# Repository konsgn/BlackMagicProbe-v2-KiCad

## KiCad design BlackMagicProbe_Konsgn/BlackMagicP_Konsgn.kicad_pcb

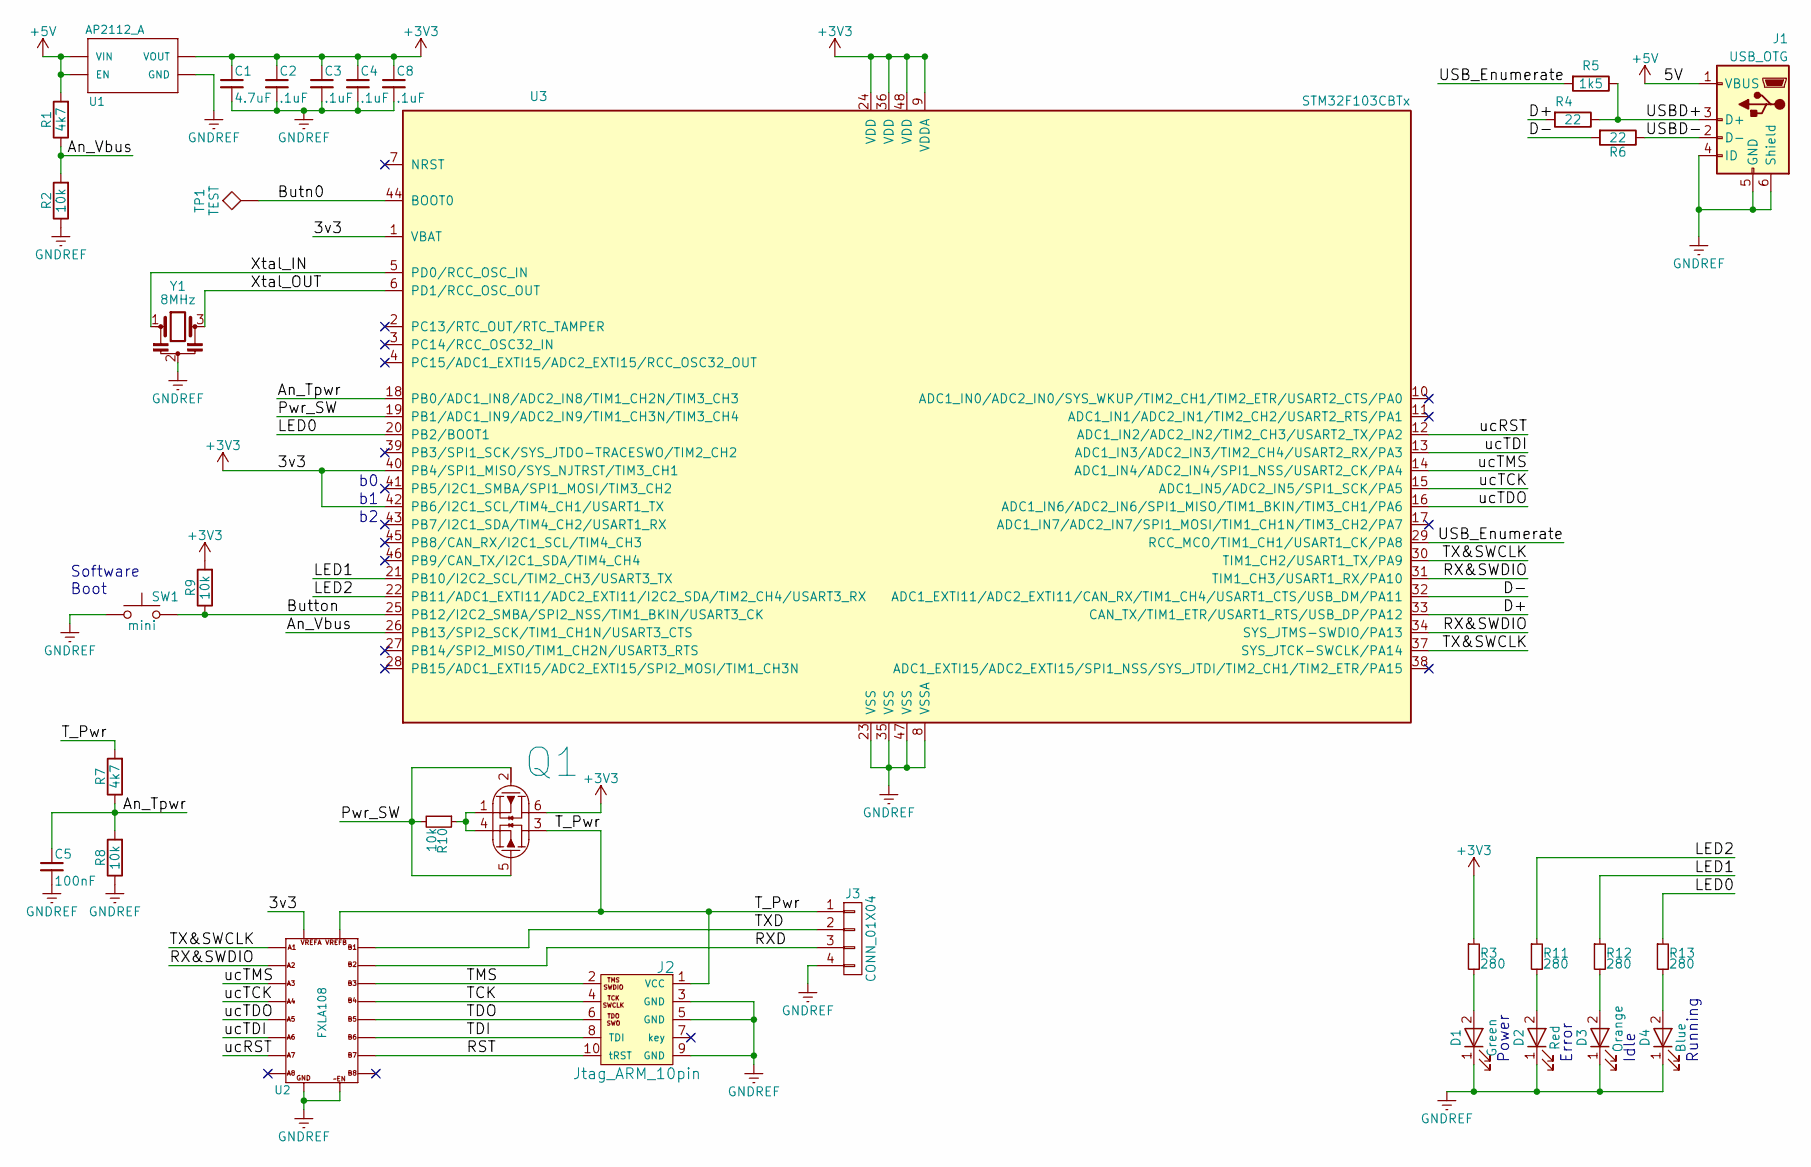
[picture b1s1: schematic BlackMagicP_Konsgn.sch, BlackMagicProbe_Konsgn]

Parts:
C1: 4.7uF; C_0603
C2, C3, C4, C8: .1uF; C_0603
C5: 100nF; C_0603
D1: Green; LED_0603
D2: Red; LED_0603
D3: Orange; LED_0603
D4: Blue; LED_0603
J1: USB_OTG; Homebrew-USB-B-MICRO-SMD_PINS
J2: Jtag_ARM_10pin; CNX_2X05X1.27_Vertical_SMD
J3: CONN_01X04; Pin_Header_Angled_1x04_Pitch2.54mm_SMD_Pin1Right
Q1: Q2-PMOS-S2G2D1S1G1D2; SOT563-6
R1, R7: 4k7; R_0603
R2, R8, R9, R10: 10k; R_0603
R3, R11, R12, R13: 280; R_0603
R4, R6: 22; R_0603
R5: 1k5; R_0603
SW1: mini; Homebrew-SMT_SPSD_5X3MM
TP1: TEST; Measurement_Point_Round-SMD-Pad_Small
U1: AP2112_A; Homebrew-SOT23-5
U2: FXLA108; Homebrew-DHVQFN20
U3: STM32F103CBTx; LQFP-48_7x7mm_Pitch0.5mm
Y1: 8MHz; Resonator_SMD_muRata_SFSKA-3pin_7.9x3.8mm_HandSoldering

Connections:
+3V3: C1.1, C2.1, C3.1, C4.1, C8.1, Q1.6, R3.1, R9.2, U1.5 (VOUT), U2.1, U3.1 (VBAT), U3.9 (VDDA), U3.24 (VDD), U3.36 (VDD), U3.40 (PB4/SPI1_MISO/SYS_NJTRST/TIM3_CH1), U3.42 (PB6/I2C1_SCL/TIM4_CH1/USART1_TX), U3.48 (VDD)
+5V: J1.1 (VBUS), R1.2, U1.1 (VIN), U1.3 (EN)
/An_Tpwr: C5.1, R7.1, R8.2, U3.18 (PB0/ADC1_IN8/ADC2_IN8/TIM1_CH2N/TIM3_CH3)
/An_Vbus: R1.1, R2.2, U3.26 (PB13/SPI2_SCK/TIM1_CH1N/USART3_CTS)
/Butn0: TP1.1, U3.44 (BOOT0)
/Button: R9.1, SW1.2, U3.25 (PB12/I2C2_SMBA/SPI2_NSS/TIM1_BKIN/USART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)
/D+: R4.2, U3.33 (CAN_TX/TIM1_ETR/USART1_RTS/USB_DP/PA12)
/D-: R6.2, U3.32 (ADC1_EXTI11/ADC2_EXTI11/CAN_RX/TIM1_CH4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)
/LED0: R13.1, U3.20 (PB2/BOOT1)
/LED1: R12.1, U3.21 (PB10/I2C2_SCL/TIM2_CH3/USART3_TX)
/LED2: R11.1, U3.22 (PB11/ADC1_EXTI11/ADC2_EXTI11/I2C2_SDA/T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)
/Pwr_SW: Q1.2, Q1.5, R10.2, U3.19 (PB1/ADC1_IN9/ADC2_IN9/TIM1_CH3N/TIM3_CH4)
/RST: J2.10 (tRST), U2.13
/RX&SWDIO: U2.3, U3.31 (TIM1_CH3/USART1_RX/PA10), U3.34 (SYS_JTMS-SWDIO/PA13)
/RXD: J3.3, U2.18
/TCK: J2.4, U2.16
/TDI: J2.8 (TDI), U2.14
/TDO: J2.6, U2.15
/TMS: J2.2, U2.17
/TX&SWCLK: U2.2, U3.30 (TIM1_CH2/USART1_TX/PA9), U3.37 (SYS_JTCK-SWCLK/PA14)
/TXD: J3.2, U2.19
/T_Pwr: J2.1 (VCC), J3.1, Q1.3, R7.2, U2.20
/USBD+: J1.3 (D+), R4.1, R5.1
/USBD-: J1.2 (D-), R6.1
/USB_Enumerate: R5.2, U3.29 (RCC_MCO/TIM1_CH1/USART1_CK/PA8)
/Xtal_IN: U3.5 (PD0/RCC_OSC_IN), Y1.1
/Xtal_OUT: U3.6 (PD1/RCC_OSC_OUT), Y1.3
/ucRST: U2.8, U3.12 (ADC1_IN2/ADC2_IN2/TIM2_CH3/USART2_TX/PA2)
/ucTCK: U2.5, U3.15 (ADC1_IN5/ADC2_IN5/SPI1_SCK/PA5)
/ucTDI: U2.7, U3.13 (ADC1_IN3/ADC2_IN3/TIM2_CH4/USART2_RX/PA3)
/ucTDO: U2.6, U3.16 (ADC1_IN6/ADC2_IN6/SPI1_MISO/TIM1_BKIN/T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)
/ucTMS: U2.4, U3.14 (ADC1_IN4/ADC2_IN4/SPI1_NSS/USART2_CK/PA4)
GNDREF: C1.2, C2.2, C3.2, C4.2, C5.2, C8.2, D1.1 (K), D2.1 (K), D3.1 (K), D4.1 (K), J1.4 (ID), J1.5 (GND), J1.6 (Shield), J2.3 (GND), J2.5 (GND), J2.9 (GND), J3.4, R2.1, R8.1, SW1.1, U1.2 (GND), U2.10, U2.11, U3.8 (VSSA), U3.23 (VSS), U3.35 (VSS), U3.47 (VSS), Y1.2
unnamed: D1.2 (A), R3.2
unnamed: D2.2 (A), R11.2
unnamed: D3.2 (A), R12.2
unnamed: D4.2 (A), R13.2
unnamed: Q1.1, Q1.4, R10.1

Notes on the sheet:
Running
Idle
Error
Power
Software Boot

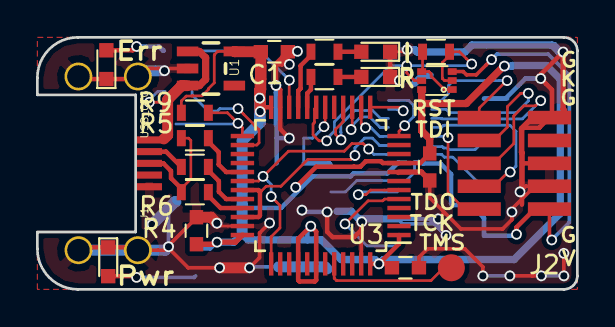
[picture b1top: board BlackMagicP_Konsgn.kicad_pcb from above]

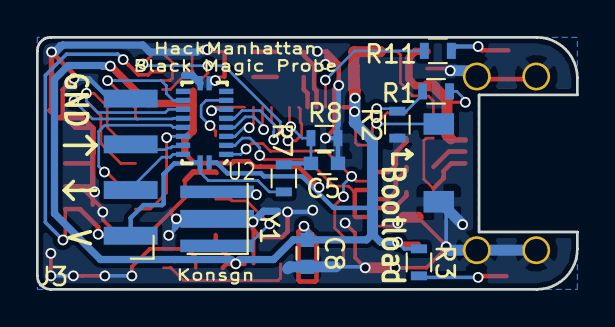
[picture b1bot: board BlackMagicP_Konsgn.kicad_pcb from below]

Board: 2 copper layers, 30.0 x 14.0 mm, 33 parts (12 on the bottom side), 38 nets.

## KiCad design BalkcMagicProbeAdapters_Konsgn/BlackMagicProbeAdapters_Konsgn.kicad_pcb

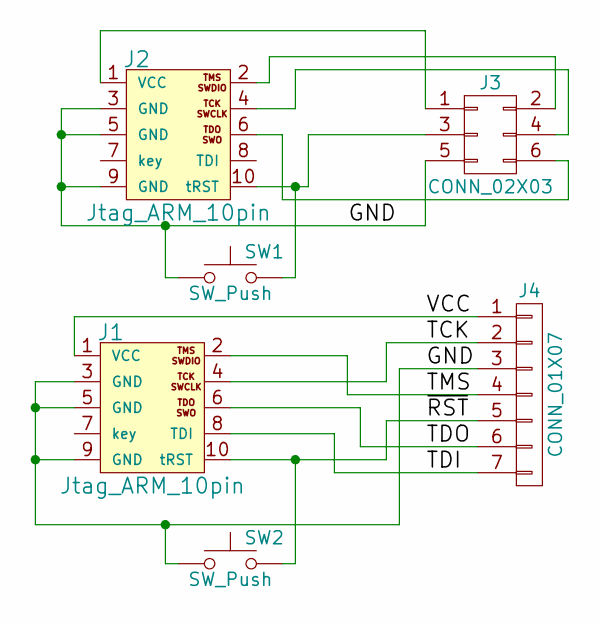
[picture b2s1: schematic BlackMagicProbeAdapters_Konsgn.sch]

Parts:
J1, J2: Jtag_ARM_10pin; CNX_2X05X1.27_Vertical_SMD
J3: CONN_02X03; Pin_Header_Straight_2x03_Pitch2.54mm_SMD
J4: CONN_01X07; Pin_Header_Angled_1x07_Pitch2.54mm
SW1, SW2: SW_Push; Homebrew-SMT_SPSD_5X3MM

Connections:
/GND: J1.3 (GND), J1.5 (GND), J1.9 (GND), J2.3 (GND), J2.5 (GND), J2.9 (GND), J3.5, J4.3, SW1.1, SW2.1
/TCK: J1.4, J4.2
/TDI: J1.8 (TDI), J4.7
/TDO: J1.6, J4.6
/TMS: J1.2, J4.4
/VCC: J1.1 (VCC), J4.1
/~RST: J1.10 (tRST), J4.5, SW2.2
unnamed: J2.1 (VCC), J3.1
unnamed: J2.2, J3.2
unnamed: J2.4, J3.4
unnamed: J2.6, J3.6
unnamed: J2.10 (tRST), J3.3, SW1.2

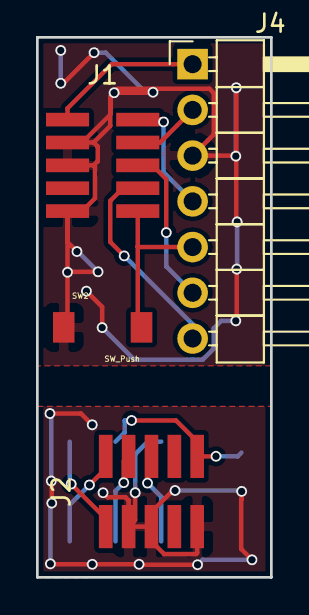
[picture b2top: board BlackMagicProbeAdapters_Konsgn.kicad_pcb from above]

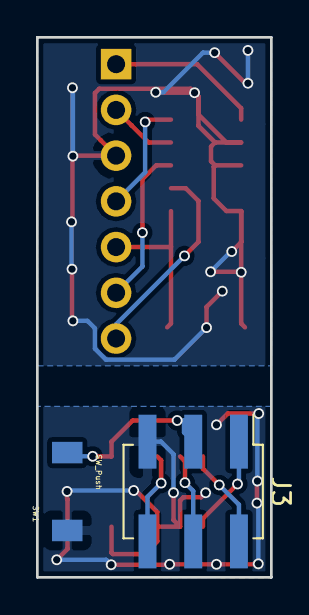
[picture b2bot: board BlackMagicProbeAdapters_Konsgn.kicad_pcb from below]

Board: 2 copper layers, 13.0 x 30.0 mm, 6 parts (2 on the bottom side), 12 nets.

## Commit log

2018-03-27 Dump of BlackMagicProbev2 Kicad_layout
